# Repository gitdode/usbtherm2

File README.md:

# usbtherm2

Simple USB thermometer and hygrometer (under construction)

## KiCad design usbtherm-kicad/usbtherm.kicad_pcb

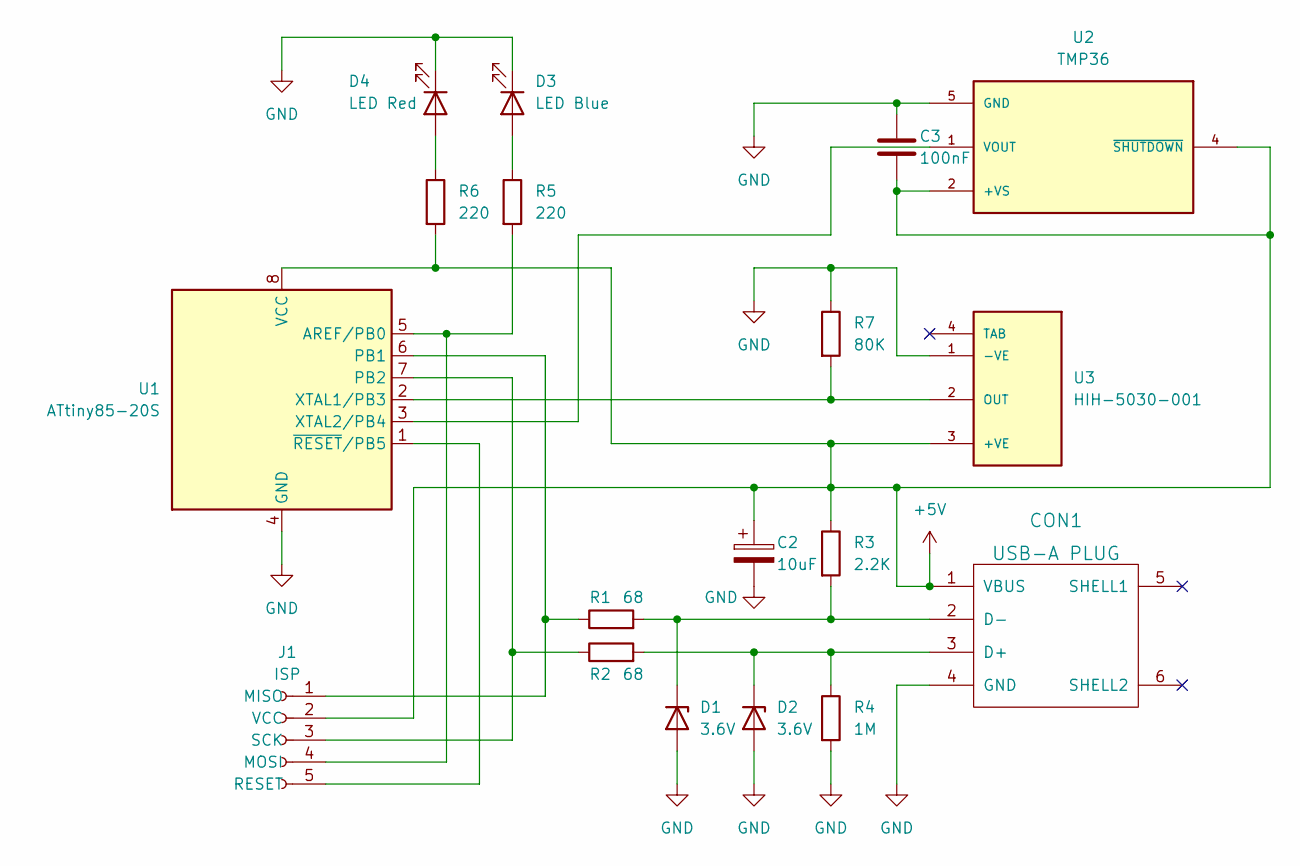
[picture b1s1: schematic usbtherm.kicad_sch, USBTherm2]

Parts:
C2: 10uF; C_1206_3216Metric_Pad1.33x1.80mm_HandSolder
C3: 100nF; C_1206_3216Metric_Pad1.33x1.80mm_HandSolder
CON1: USB-A PLUG; USB_A_PLUG
D1, D2: 3.6V; D_SOD-123
D3: LED Blue; LED_1206_3216Metric_Pad1.42x1.75mm_HandSolder
D4: LED Red; LED_1206_3216Metric_Pad1.42x1.75mm_HandSolder
J1: ISP; PinSocket_1x05_P2.54mm_Vertical
R1, R2: 68; R_0805_2012Metric_Pad1.20x1.40mm_HandSolder
R3: 2.2K; R_0805_2012Metric_Pad1.20x1.40mm_HandSolder
R4: 1M; R_0805_2012Metric_Pad1.20x1.40mm_HandSolder
R5, R6: 220; R_0805_2012Metric_Pad1.20x1.40mm_HandSolder
R7: 80K; R_0805_2012Metric_Pad1.20x1.40mm_HandSolder
U1: ATtiny85-20S; SOIC-8W_5.3x5.3mm_P1.27mm
U2: TMP36; SOT95P280X145-5N; PARTREV H
U3: HIH-5030-001; HONEYWELL_HIH-5030-001

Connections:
+5V: C2.1, C3.2, CON1.1 (VBUS), J1.2 (VCC), R3.1, R6.2, U1.8 (VCC), U2.2 (+VS), U2.4 (~SHUTDOWN), U3.3 (+VE)
GND: C2.2, C3.1, CON1.4 (GND), D1.2 (A), D2.2 (A), D3.1 (K), D4.1 (K), R4.2, R7.1, U1.4 (GND), U2.5 (GND), U3.1 (-VE)
unnamed: CON1.2 (D-), D1.1 (K), R1.2, R3.2
unnamed: CON1.3 (D+), D2.1 (K), R2.2, R4.1
unnamed: D3.2 (A), R5.1
unnamed: D4.2 (A), R6.1
unnamed: J1.1 (MISO), R1.1, U1.6 (PB1)
unnamed: J1.3 (SCK), R2.1, U1.7 (PB2)
unnamed: J1.4 (MOSI), R5.2, U1.5 (AREF/PB0)
unnamed: R7.2, U1.2 (XTAL1/PB3), U3.2 (OUT)
unnamed: J1.5 (RESET), U1.1 (~RESET/PB5)
unnamed: U1.3 (XTAL2/PB4), U2.1 (VOUT)

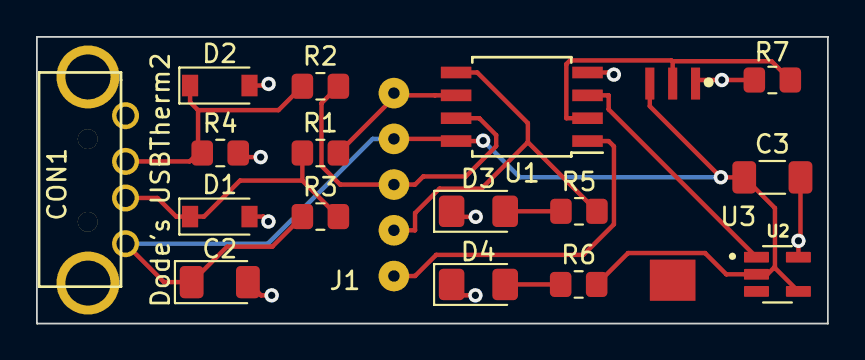
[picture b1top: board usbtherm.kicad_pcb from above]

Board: 2 copper layers, 43.9 x 15.9 mm, 18 parts (0 on the bottom side), 12 nets.

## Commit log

2023-01-15 Initial refactoring of usbtherm(1)
    - calibrate oscillator at 16.5 MHz to free pins needed for ADC from crystal
    - prepare for measuring at different pins
    - don't initialize average to 20 °C
2023-01-22 implement measuring and calculating humidity + fixes and improvements
2023-01-24 add LED flashing at each measurement, improve comments
2023-01-24 don't answer request when not yet measured after device connect
2023-01-25 comment cosmetic, fix data types
2023-01-26 add NetBeans project
2023-01-31 add schematic
2023-02-04 add PCB
2023-02-21 make readings more inert, fix overflow in temperature compensation of humidity
